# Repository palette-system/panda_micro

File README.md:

# PandaMicro (🐼micro)

<br><br><br>

## 説明

PandaMicro は MCP23017 を使用した ProMicro サイズのIOエキスパンダモジュールです。  
基板にTRRSジャックが取り付けられているのが特徴で、TRRSを利用してI2C通信を行います。  
ピンの配列は可能な限りProMicroと互換するよう設計していますが一部利用できないピンがあるため注意して下さい。  
<br><br>

## TRRSジャック

<table>
  <tr>
    <td>1</td>
    <td>T</td>
    <td>SCL</td>
    <td rowspan="4"></td>
  </tr>
  <tr>
    <td>2</td>
    <td>R</td>
    <td>SDA</td>
  </tr>
  <tr>
    <td>3</td>
    <td>R</td>
    <td>VCC</td>
  </tr>
  <tr>
    <td>4</td>
    <td>S</td>
    <td>GND</td>
  </tr>
</table>
<br><br>

## ProMicroピン互換表

<table>
  <tr>
    <th>No</th>
    <th>ProMicro</th>
    <th>PandaMicro</th>
    <td rowspan="13">　</td>
    <th>No</th>
    <th>ProMicro</th>
    <th>PandaMicro</th>
  </tr>
  <tr>
    <td>1</td>
    <td>D3</td>
    <td>NC</td>
    <td>24</td>
    <td>RAW</td>
    <td>VCC</td>
  </tr>
  <tr>
    <td>2</td>
    <td>D2</td>
    <td>NC</td>
    <td>23</td>
    <td>GND</td>
    <td>GND</td>
  </tr>
  <tr>
    <td>3</td>
    <td>GND</td>
    <td>GND</td>
    <td>22</td>
    <td>RESET</td>
    <td>NC</td>
  </tr>
  <tr>
    <td>4</td>
    <td>GND</td>
    <td>GND</td>
    <td>21</td>
    <td>VCC</td>
    <td>VCC</td>
  </tr>
  <tr>
    <td>5</td>
    <td>D1</td>
    <td>GA0</td>
    <td>20</td>
    <td>F4</td>
    <td>GB7</td>
  </tr>
  <tr>
    <td>6</td>
    <td>D0</td>
    <td>GA1</td>
    <td>19</td>
    <td>F5</td>
    <td>GB6</td>
  </tr>
  <tr>
    <td>7</td>
    <td>D4</td>
    <td>GA2</td>
    <td>18</td>
    <td>F6</td>
    <td>GB5</td>
  </tr>
  <tr>
    <td>8</td>
    <td>C6</td>
    <td>GA3</td>
    <td>17</td>
    <td>F7</td>
    <td>GB4</td>
  </tr>
  <tr>
    <td>9</td>
    <td>D7</td>
    <td>GA4</td>
    <td>16</td>
    <td>B1</td>
    <td>GB3</td>
  </tr>
  <tr>
    <td>10</td>
    <td>E6</td>
    <td>GA5</td>
    <td>15</td>
    <td>F3</td>
    <td>GB2</td>
  </tr>
  <tr>
    <td>11</td>
    <td>B4</td>
    <td>GA6</td>
    <td>14</td>
    <td>B2</td>
    <td>GB1</td>
  </tr>
  <tr>
    <td>12</td>
    <td>B5</td>
    <td>GA7</td>
    <td>13</td>
    <td>B6</td>
    <td>GB0</td>
  </tr>
</table>
<br><br>

## アドレスジャンパーピンの設定

I2C上に複数のpanda_microを接続できるので、どのpanda_microが何番目のpanda_microか判断するために必ずアドレスの設定が必要になります。<br>
アドレスの設定は画像部分のジャンパーピンをはんだ付けして行って下さい。<br><br>
※ 1つしか接続しない場合でもアドレス設定をしないと使用できません。<br><br>

<table><tr><td>
　
</td><td>

</td></tr></table>
<br><br>

## 対応キーボード

使用したいキーボードの基板データが公開されていればProMicro部分の、画像で言う青い部分でキーの入力を取得しているキーボードは対応しています(Duplex-Matrixは非対応)、オレンジ色の部分でキー入力をしているキーボードは非対応になります(LEDのデータや、左右の通信で使用している分には問題ない)。<br>

<br><br>

■ 使用できる<br>
・スイッチに直繋ぎ(IOピン→スイッチ→GND)<br>
・通常Matrix<br>
・コンスル―<br>
<br>

■ 使用できない<br>
・Duplex-Matrix<br>
・OLED<br>
・トラックボール<br>
・ロータリーエンコーダー<br>
・RGB-LED<br>

## 使用パーツ

<table>
  <tr>
    <th>部品名</th>
    <td>表記</td>
    <td>容量 / 型番</td>
  </tr>
  <tr>
    <th>TRRSジャック</th>
    <td>　</td>
    <td>PJ320D</td>
  </tr>
  <tr>
    <th>IOエキスパンダ</th>
    <td>U1</td>
    <td>MCP23017-E/SS</td>
  </tr>
  <tr>
    <th>コンデンサ</th>
    <td>C1</td>
    <td>0.1μF（サイズ：2012）</td>
  </tr>
  <tr>
    <th>I2Cプルアップ抵抗</th>
    <td>R1、R2</td>
    <td>2.2kΩ（サイズ：2012）</td>
  </tr>
</table>
<br><br>

## 詳細情報

電圧：　1.8V　～　5.5V  
信号：　I2C　（～1.7MHz）
サイズ：　width 17.78mm　×　height 33.02
<br><br>

## 動かない時に確認するポイント

・ジャンパーピンでアドレス設定は必須です。このページの上の方にアドレス設定の説明があるので必ずアドレス設定をして下さい。<br><br>
・TRRSは４極の物のみ対応しています。ケーブルのピンが４極かチェックして下さい。<br><br>
・キーボードに接続した時のpanda_microの表、裏が逆になっていない事を確認して下さい。(キーボードにピンの名前が書いてあると思うので必ずpanda_microに書いてあるピンと合うように接続して下さい)<br><br>
・ケーブルの長さが1mを超えるものだとI2Cのプルアップが足りなくなる場合があるので、他のキーボードで使えていたケーブルだったとしても何本か別のケーブルを試してみて下さい。ケーブルが短い方が繋がりやすいです。<br><br>
・キーボードに付いているLEDやOLEDに電流を持って行かれてIOエキスパンダが電流不足で動かない事があります。panda_microのVCC（Vと書いてあるピン）の所のコンスル―ピンを抜くなどしてキーボードとVCCが繋がらないようにしてみて下さい。<br><br>

## 写真

<br><br>
<br><br>
<br><br>

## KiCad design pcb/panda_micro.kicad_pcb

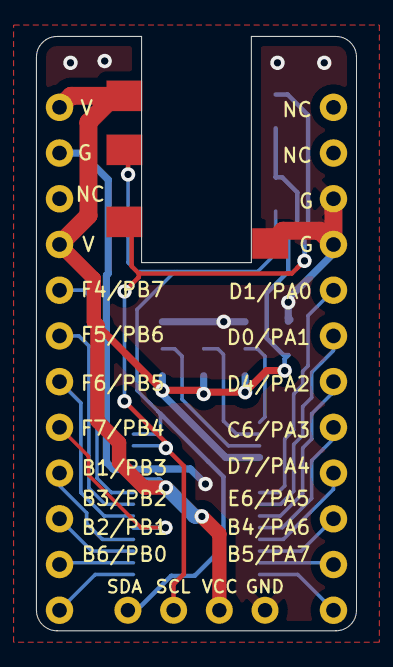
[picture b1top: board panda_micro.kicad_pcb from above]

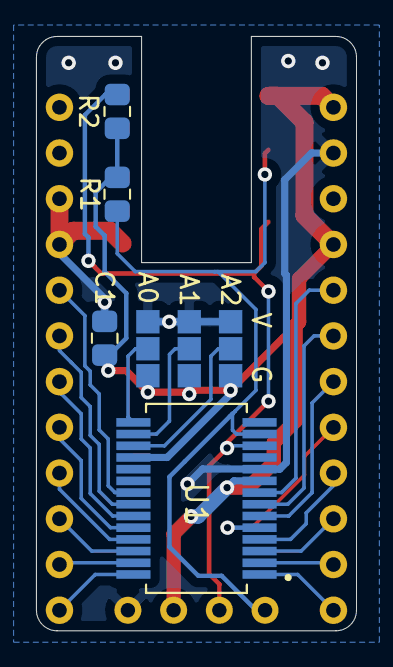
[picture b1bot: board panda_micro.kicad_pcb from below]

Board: 2 copper layers, 17.8 x 33.0 mm, 6 parts (4 on the bottom side), 20 nets.

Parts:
C1: 1kΩ; R_0805_2012Metric1.2
J1: MJ-4PP-9; MJ-4PP-9_1side
R1, R2: 1kΩ; R_0805_2012Metric1.2
U1: ProMicro; ProMicro_v3
U1#2: SOP65P780X200-28N

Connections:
GND: C1.2, J1.A, U1.3, U1.4, U1.23, U1#2.10
KEY1: U1.5, U1#2.21
KEY2: U1.6, U1#2.22
KEY3: U1.7, U1#2.23
KEY4: U1.8, U1#2.24
KEY5: U1.9, U1#2.25
KEY6: U1.10, U1#2.26
KEY7: U1.11, U1#2.27
KEY8: U1.12, U1#2.28
KEY9: U1.13, U1#2.1
KEY10: U1.14, U1#2.2
KEY11: U1.15, U1#2.3
KEY12: U1.16, U1#2.4
KEY13: U1.17, U1#2.5
KEY14: U1.18, U1#2.6
KEY15: U1.19, U1#2.7
KEY16: U1.20, U1#2.8
SCL: J1.D, R2.2, U1#2.12
SDA: J1.C, R1.2, U1#2.13
VCC: C1.1, J1.B, R1.1, R2.1, U1.21, U1.24, U1#2.9, U1#2.18

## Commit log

2022-05-26 add panda_micro
2022-06-22 update image
2022-06-23 add num
2022-06-25 add detail
2022-06-25 add size
2022-08-12 update doc
